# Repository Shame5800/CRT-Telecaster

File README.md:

Members

Shane Pomajambo, Electrical Engineering Student (2026)
Shanepomajambo16@vt.edu

Mentor

Arthur Ball

Current Status

IN PROGRESS

Project Overview

The purpose of this project is to create the CRT Telecaster guitars used by the Band ELECTRONICOS FANTASTICOS (https://www.youtube.com/@ELECTRONICOSFANTASTICOS_YT). The instrument sends 0V to 1V audio signals such as square, sine, and triangle waves to the video jack of a CRT television. This visualizes the waveform in the form of white and black bars, where white is high and black is low. Since CRT televisions are significant sources of electric fields, the audio signal fed into the video jack will become part of these fields, and the field’s rate of change will be the audio’s frequency with the CRT's internal frequencies. 

The note playing is caused by the concept of capacitive coupling. When the user touches the screen of the CRT, the screen and the user's hand form a parallel plate capacitor. On the board, there's an op-amp buffer that takes its input from a small trace and sends the output to an external speaker. When the instrument is in playing position, the trace is in proximity to the user's torso and is far away from any ground fills. This forms a series capacitor network formed by the hand-to-screen capacitance, the torso-to-trace capacitance, and the parasitic capacitance of the op-amp buffer trace. The changing E-field of the CRT creates displacement current on the network, which means the audio signal input to the CRT can be picked up by the capacitor network and sent to the speaker. Since the smallest capacitor in a series capacitor network sees the largest amount of voltage, the user can then change the volume of the note by bringing their hand closer or farther to the screen, which changes the capacitance ratios of the network that determine how much the op-amp buffer sees. 

The design of this instrument uses a driver PCB equipped with an ESP32 and a button array PCB meant to resemble a guitar fretboard. The board is equipped with 4 DAC channels and a non-inverting summing amplifier that leads to the CRT video input. In order to determine the fret being played, the fretboard PCB connects resistor dividers that are read by the ESP32’s ADCs. Each fret is designed to be 0.15V away from eachother, so that the ESP32’s 12-bit resolution sees it as being 200 counts away from eachother and has enough space to provide accurate readings. Once the user inputs a note on the fretboard, the ESP32 uses interrupt-style code to communicate to the DAC’s and have them output the musical frequencies. The driver board also comes equipped with a variety of switches and potentiometers to handle different musical effects and synth waveform structures. The user can alternate between 8 wave types, octaver, and warble effects, as well as bass, 5-string bass, and guitar options.

As of Summer 2026, the V2 of this project has finished development, and the V3 platform is currently in development. The next variation aims to improve mistakes from the previous iteration, including easier-to-access switches and a more ergonomic fretboard, and fixing SPI bus issues encountered in V2’s integration. It also aims to introduce new features, such as a touchscreen LCD allowing the user to draw the waveform that will be generated, more audio effects, and an internal programmable drum machine connected to the CRT’s speakers.

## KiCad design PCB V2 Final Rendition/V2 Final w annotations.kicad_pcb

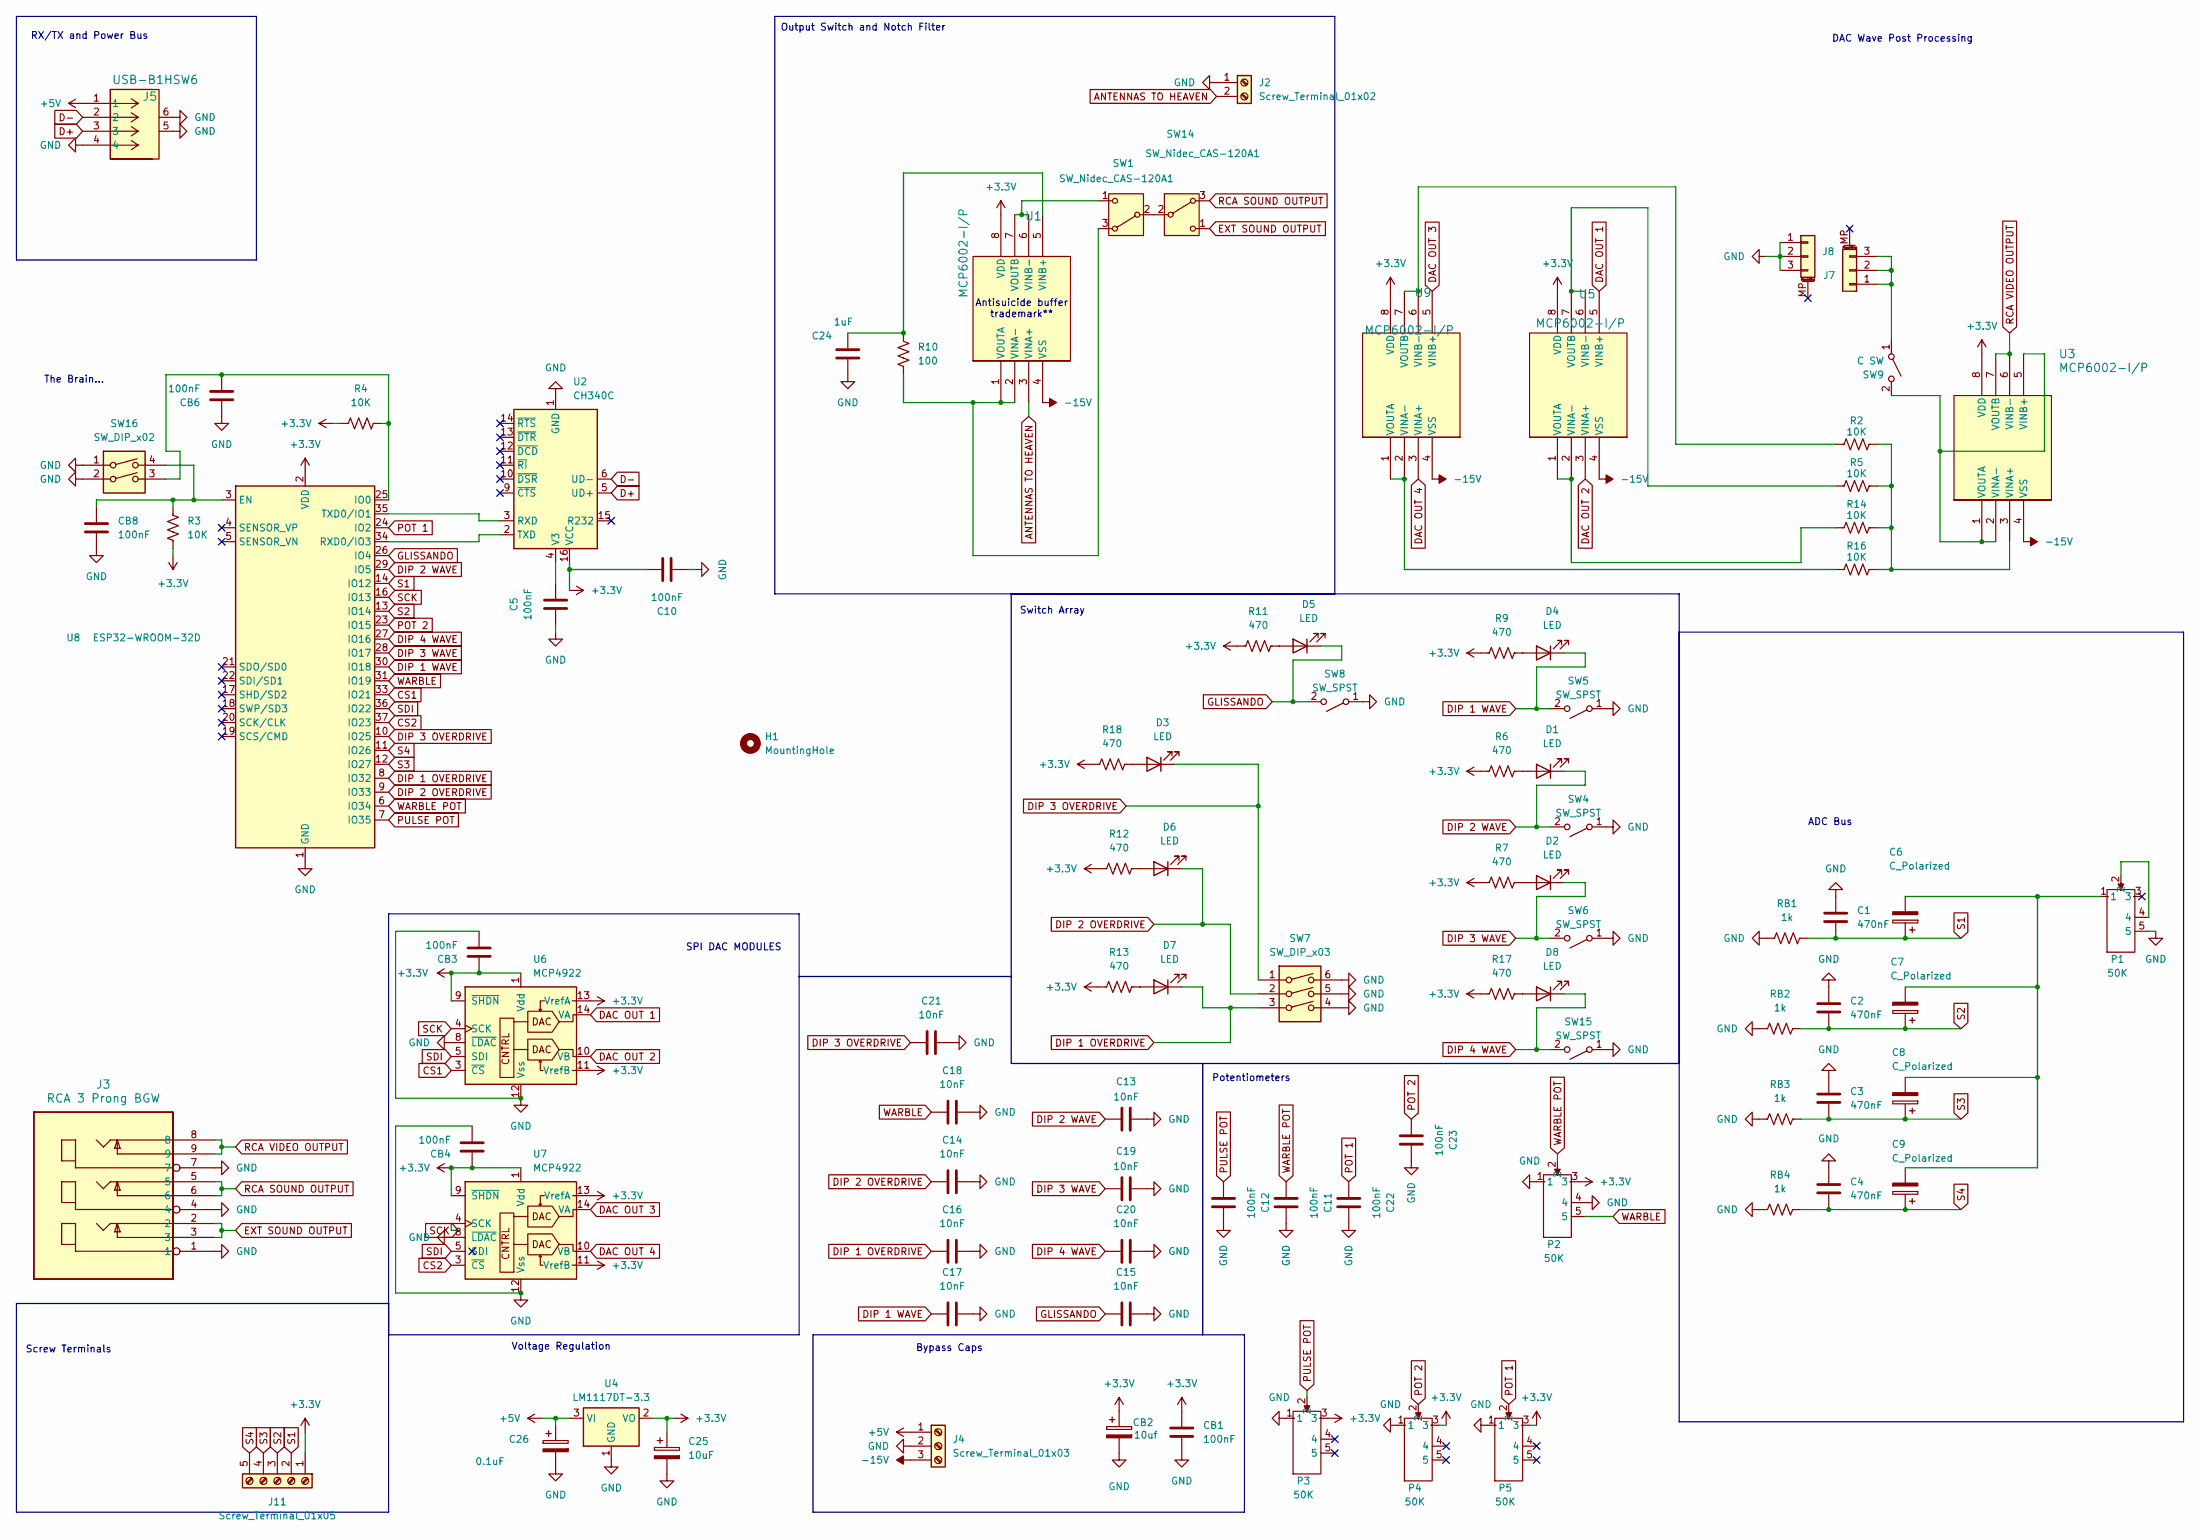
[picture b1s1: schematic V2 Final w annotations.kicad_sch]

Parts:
C1, C2, C3, C4: 470nF; C_Disc_D8.0mm_W2.5mm_P5.00mm
C5, C10, C11, C12, C22, C23: 100nF; C_0805_2012Metric_Pad1.18x1.45mm_HandSolder
C6, C7, C8, C9: C_Polarized; CP_Radial_D4.0mm_P2.00mm
C13, C14, C15, C16, C17, C18, C19, C20, C21: 10nF; C_0805_2012Metric_Pad1.18x1.45mm_HandSolder
C24: 1uF; C_Disc_D8.0mm_W2.5mm_P5.00mm
C25: 10uF; CP_Radial_D4.0mm_P2.00mm
C26: 0.1uF; CP_Radial_D4.0mm_P2.00mm
CB1, CB6: 100nF; C_0805_2012Metric_Pad1.18x1.45mm_HandSolder
CB2: 10uf; CP_Radial_D4.0mm_P2.00mm
CB3, CB4, CB8: 100nF; C_0805_2012Metric
D1, D2, D4, D5, D8: LED; LED_D3.0mm
D3, D6, D7: LED; LED_0805_2012Metric
H1: MountingHole; MountingHole_3.2mm_M3
J2: Screw_Terminal_01x02; TerminalBlock_MaiXu_MX126-5.0-02P_1x02_P5.00mm
J3: RCA 3 Prong BGW; RCA 3 Prong
J4: Screw_Terminal_01x03; TerminalBlock_MaiXu_MX126-5.0-03P_1x03_P5.00mm
J5: USB-B1HSW6; USB B Port
J7, J8: Conn_01x03_MountingPin; PinSocket_1x03_P2.54mm_Vertical
J11: Screw_Terminal_01x05; TerminalBlock_MaiXu_MX126-5.0-05P_1x05_P5.00mm
P1, P2, P3, P4, P5: 50K; ALPS POT SWITCH
R2, R5, R14, R16: 10K; R_Axial_DIN0207_L6.3mm_D2.5mm_P7.62mm_Horizontal
R3, R4: 10K; R_0805_2012Metric
R6, R7, R9, R11, R17: 470; R_Axial_DIN0207_L6.3mm_D2.5mm_P7.62mm_Horizontal
R10: 100; R_Axial_DIN0207_L6.3mm_D2.5mm_P7.62mm_Horizontal
R12, R13, R18: 470; R_0805_2012Metric
RB1, RB2, RB3, RB4: 1k; R_Axial_DIN0207_L6.3mm_D2.5mm_P7.62mm_Horizontal
SW1, SW14: SW_Nidec_CAS-120A1; SW_Slide_SPDT_Straight_CK_OS102011MS2Q
SW4, SW5, SW6, SW8, SW15: SW_SPST; SW_Slide_SPDT_Straight_CK_OS102011MS2Q
SW7: SW_DIP_x03; SW_DIP_SPSTx03_Slide_9.78x9.8mm_W7.62mm_P2.54mm
SW9: C SW; SW_Slide_SPDT_Straight_CK_OS102011MS2Q
SW16: SW_DIP_x02; SW_DIP_SPSTx02_Slide_9.78x7.26mm_W7.62mm_P2.54mm
U1, U3, U5, U9: MCP6002-I/P; MCP6002
U2: CH340C; SOIC-16_3.9x9.9mm_P1.27mm
U4: LM1117DT-3.3; SOT-223-3_TabPin2
U6, U7: MCP4922
U8: ESP32-WROOM-32D; esp32 WROOM without that FUCKASS attenna

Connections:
+3.3V: C10.1, C25.1, CB1.2, CB2.1, CB3.2, CB4.2, J11.1, P2.3, P3.3, P4.3, P5.3, R3.2, R4.1, R6.1, R7.1, R9.1, R11.1, R12.1, R13.1, R17.1, R18.1, U1.8 (VDD), U2.16 (VCC), U3.8 (VDD), U4.2 (VO), U5.8 (VDD), U6.1 (Vdd), U6.9 (~SHDN), U6.11 (VrefB), U6.13 (VrefA), U7.1 (Vdd), U7.9 (~SHDN), U7.11 (VrefB), U7.13 (VrefA), U8.2 (VDD), U9.8 (VDD)
+5V: C26.1, J4.1, J5.1, U4.3 (VI)
-15V: J4.3, U1.4 (VSS), U3.4 (VSS), U5.4 (VSS), U9.4 (VSS)
ANTENNAS TO HEAVEN: J2.2, U1.3 (VINA+)
CS1: U6.3 (~CS), U8.33 (IO21)
CS2: U7.3 (~CS), U8.37 (IO23)
D+: J5.3, U2.5 (UD+)
D-: J5.2, U2.6 (UD-)
DAC OUT 1: U5.5 (VINB+), U6.14 (VA)
DAC OUT 2: U5.3 (VINA+), U6.10 (VB)
DAC OUT 3: U7.14 (VA), U9.5 (VINB+)
DAC OUT 4: U7.10 (VB), U9.3 (VINA+)
DIP 1 OVERDRIVE: C16.2, D7.1 (K), SW7.3, U8.8 (IO32)
DIP 1 WAVE: C17.2, D4.1 (K), SW5.2 (B), U8.30 (IO18)
DIP 2 OVERDRIVE: C14.2, D6.1 (K), SW7.2, U8.9 (IO33)
DIP 2 WAVE: C13.2, D1.1 (K), SW4.2 (B), U8.29 (IO5)
DIP 3 OVERDRIVE: C21.2, D3.1 (K), SW7.1, U8.10 (IO25)
DIP 3 WAVE: C19.2, D2.1 (K), SW6.2 (B), U8.28 (IO17)
DIP 4 WAVE: C20.2, D8.1 (K), SW15.2 (B), U8.27 (IO16)
EXT SOUND OUTPUT: J3.2, J3.3, SW14.1 (C)
GLISSANDO: C15.2, D5.1 (K), SW8.2 (B), U8.26 (IO4)
GND: C1.1, C2.1, C3.1, C4.1, C5.2, C10.2, C11.1, C12.1, C13.1, C14.1, C15.1, C16.1, C17.1, C18.1, C19.1, C20.1, C21.1, C22.1, C23.1, C24.1, C25.2, C26.2, CB1.1, CB2.2, CB3.1, CB4.1, CB6.2, CB8.1, J2.1, J3.1, J3.4, J3.7, J4.2, J5.4, J5.5, J5.6, J8.1, J8.2, J8.3, P1.5, P2.1, P2.4, P3.1, P4.1, P5.1, RB1.1, RB2.1, RB3.1, RB4.1, SW4.1 (A), SW5.1 (A), SW6.1 (A), SW7.4, SW7.5, SW7.6, SW8.1 (A), SW15.1 (A), SW16.1, SW16.2, U2.1 (GND), U4.1 (GND), U6.8 (~LDAC), U6.12 (Vss), U7.8 (~LDAC), U7.12 (Vss), U8.1 (GND), U8.15 (GND), U8.38 (GND), U8.39 (GND)
unnamed: C6.2, C7.2, C8.2, C9.2, P1.1
unnamed: D1.2 (A), R6.2
unnamed: D2.2 (A), R7.2
unnamed: D3.2 (A), R18.2
unnamed: D4.2 (A), R9.2
unnamed: D5.2 (A), R11.2
unnamed: D6.2 (A), R12.2
unnamed: D7.2 (A), R13.2
unnamed: D8.2 (A), R17.2
unnamed: J7.1, J7.2, J7.3, SW9.1 (A)
unnamed: P1.2, P1.4
unnamed: R10.1, SW1.3 (A), U1.1 (VOUTA), U1.2 (VINA-)
unnamed: SW1.2 (B), SW14.2 (B)
unnamed: SW1.1 (C), U1.6 (VINB-), U1.7 (VOUTB)
unnamed: SW9.2 (B), U3.1 (VOUTA), U3.2 (VINA-), U3.5 (VINB+)
unnamed: C24.2, R10.2, U1.5 (VINB+)
unnamed: U2.3 (RXD), U8.35 (TXD0/IO1)
unnamed: U2.2 (TXD), U8.34 (RXD0/IO3)
unnamed: C5.1, U2.4 (V3)
unnamed: R2.2, R5.2, R14.2, R16.2, U3.3 (VINA+)
unnamed: R14.1, U5.1 (VOUTA), U5.2 (VINA-)
unnamed: R5.1, U5.6 (VINB-), U5.7 (VOUTB)
unnamed: CB8.2, R3.1, SW16.4, U8.3 (EN)
unnamed: CB6.1, R4.2, SW16.3, U8.25 (IO0)
unnamed: R16.1, U9.1 (VOUTA), U9.2 (VINA-)
unnamed: R2.1, U9.6 (VINB-), U9.7 (VOUTB)
POT 1: C22.2, P5.2, U8.24 (IO2)
POT 2: C23.2, P4.2, U8.23 (IO15)
PULSE POT: C12.2, P3.2, U8.7 (IO35)
RCA SOUND OUTPUT: J3.5, J3.6, SW14.3 (A)
RCA VIDEO OUTPUT: J3.8, J3.9, U3.6 (VINB-), U3.7 (VOUTB)
S1: C1.2, C6.1, J11.2, RB1.2, U8.14 (IO12)
S2: C2.2, C7.1, J11.3, RB2.2, U8.13 (IO14)
S3: C3.2, C8.1, J11.4, RB3.2, U8.12 (IO27)
S4: C4.2, C9.1, J11.5, RB4.2, U8.11 (IO26)
SCK: U6.4 (SCK), U7.4 (SCK), U8.16 (IO13)
SDI: U6.5 (SDI), U7.5 (SDI), U8.36 (IO22)
WARBLE: C18.2, P2.5, U8.31 (IO19)
WARBLE POT: C11.2, P2.2, U8.6 (IO34)

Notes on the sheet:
ADC Bus
Potentiometers
Output Switch and Notch Filter
Switch Array
Antisuicide buffer trademark**
SPI DAC MODULES
DAC Wave Post Processing
Screw Terminals
Voltage Regulation
Bypass Caps
The Brain...
RX/TX and Power Bus

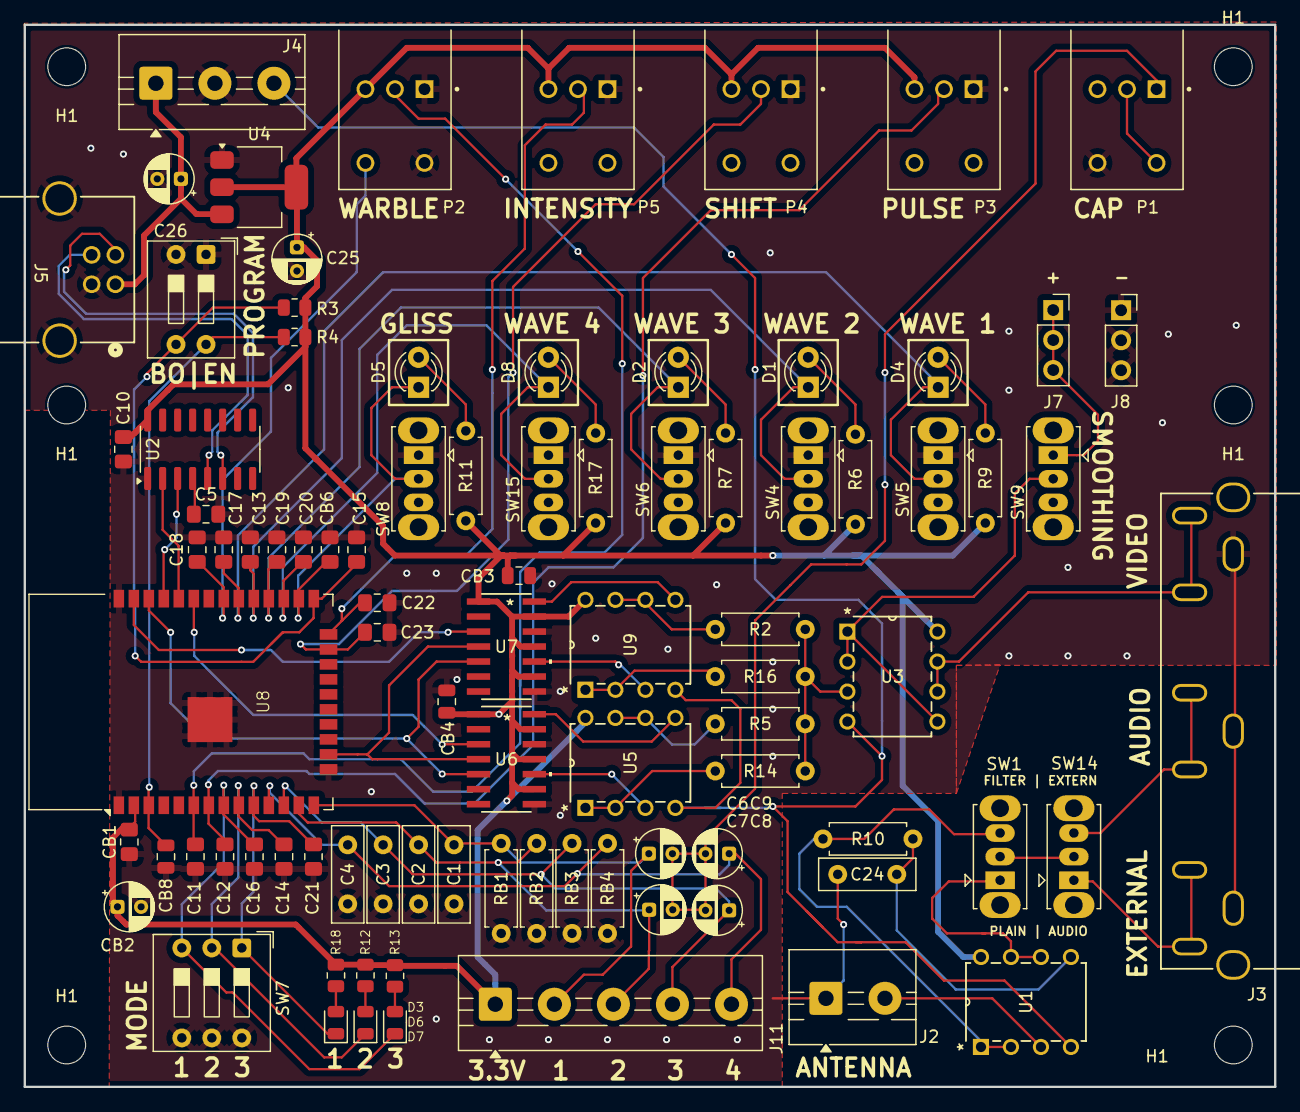
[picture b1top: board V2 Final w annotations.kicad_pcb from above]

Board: 2 copper layers, 105.9 x 89.9 mm, 96 parts (0 on the bottom side), 61 nets.

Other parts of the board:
H1#2, H1#3, H1#4, H1#5, H1#6: MountingHole; MountingHole_3.2mm_M3

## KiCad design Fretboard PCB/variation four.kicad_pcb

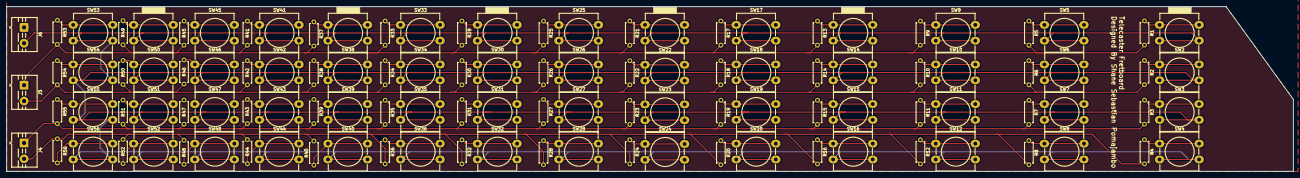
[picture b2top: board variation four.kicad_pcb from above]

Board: 2 copper layers, 406.2 x 52.0 mm, 115 parts (0 on the bottom side), 61 nets.

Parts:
J4, J5, J6: Screw_Terminal_01x02; TerminalBlock_MaiXu_MX126-5.0-02P_1x02_P5.00mm
R1, R2, R3, R4: 5K; R_Axial_DIN0207_L6.3mm_D2.5mm_P7.62mm_Horizontal
R5, R6, R7, R8: 3.6K; R_Axial_DIN0207_L6.3mm_D2.5mm_P7.62mm_Horizontal
R9, R10, R11, R12: 3K; R_Axial_DIN0207_L6.3mm_D2.5mm_P7.62mm_Horizontal
R13, R14, R15, R16: 2.2K; R_Axial_DIN0207_L6.3mm_D2.5mm_P7.62mm_Horizontal
R17, R18, R19, R20: 1.8K; R_Axial_DIN0207_L6.3mm_D2.5mm_P7.62mm_Horizontal
R21, R22, R23, R24: 1.5K; R_Axial_DIN0207_L6.3mm_D2.5mm_P7.62mm_Horizontal
R25, R26, R27, R28: 1.2K; R_Axial_DIN0207_L6.3mm_D2.5mm_P7.62mm_Horizontal
R29, R30, R31, R32: 1K; R_Axial_DIN0207_L6.3mm_D2.5mm_P7.62mm_Horizontal
R33, R34, R35, R36: 820; R_Axial_DIN0207_L6.3mm_D2.5mm_P7.62mm_Horizontal
R37, R38, R39, R40: 680; R_Axial_DIN0207_L6.3mm_D2.5mm_P7.62mm_Horizontal
R41, R42, R43, R44: 560; R_Axial_DIN0207_L6.3mm_D2.5mm_P7.62mm_Horizontal
R45, R46, R47, R48: 390; R_Axial_DIN0207_L6.3mm_D2.5mm_P7.62mm_Horizontal
R49, R50, R51, R52: 330; R_Axial_DIN0207_L6.3mm_D2.5mm_P7.62mm_Horizontal
R53, R54, R55, R56: 270; R_Axial_DIN0207_L6.3mm_D2.5mm_P7.62mm_Horizontal
SW1, SW2, SW3, SW4, SW5, SW6, SW7, SW8, SW9, SW10, SW11, SW12, SW13, SW14, SW15, SW16, SW17, SW18, SW19, SW20, SW21, SW22, SW23, SW24, SW25, SW26, SW27, SW28, SW29, SW30, SW31, SW32, SW33, SW34, SW35, SW36, SW37, SW38, SW39, SW40, SW41, SW42, SW43, SW44, SW45, SW46, SW47, SW48, SW49, SW50, SW51, SW52, SW53, SW54, SW55, SW56: SW_Push; SW_PUSH-12mm_Wuerth-430476085716

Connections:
+3.3V: J6.2, SW1.2, SW2.2, SW3.2, SW4.2, SW5.2, SW6.2, SW7.2, SW8.2, SW9.2, SW10.2, SW11.2, SW12.2, SW13.2, SW14.2, SW15.2, SW16.2, SW17.2, SW18.2, SW19.2, SW20.2, SW21.2, SW22.2, SW23.2, SW24.2, SW25.2, SW26.2, SW27.2, SW28.2, SW29.2, SW30.2, SW31.2, SW32.2, SW33.2, SW34.2, SW35.2, SW36.2, SW37.2, SW38.2, SW39.2, SW40.2, SW41.2, SW42.2, SW43.2, SW44.2, SW45.2, SW46.2, SW47.2, SW48.2, SW49.2, SW50.2, SW51.2, SW52.2, SW53.2, SW54.2, SW55.2, SW56.2
unnamed: R1.1, SW1.1
unnamed: R2.1, SW2.1
unnamed: R3.1, SW3.1
unnamed: R4.1, SW4.1
unnamed: R5.1, SW5.1
unnamed: R6.1, SW6.1
unnamed: R7.1, SW7.1
unnamed: R8.1, SW8.1
unnamed: R9.1, SW9.1
unnamed: R10.1, SW10.1
unnamed: R11.1, SW11.1
unnamed: R12.1, SW12.1
unnamed: R13.1, SW13.1
unnamed: R14.1, SW14.1
unnamed: R15.1, SW15.1
unnamed: R16.1, SW16.1
unnamed: R17.1, SW17.1
unnamed: R18.1, SW18.1
unnamed: R19.1, SW19.1
unnamed: R20.1, SW20.1
unnamed: R21.1, SW21.1
unnamed: R22.1, SW22.1
unnamed: R23.1, SW23.1
unnamed: R24.1, SW24.1
unnamed: R25.1, SW25.1
unnamed: R26.1, SW26.1
unnamed: R27.1, SW27.1
unnamed: R28.1, SW28.1
unnamed: R29.1, SW29.1
unnamed: R30.1, SW30.1
unnamed: R31.1, SW31.1
unnamed: R32.1, SW32.1
unnamed: R33.1, SW33.1
unnamed: R34.1, SW34.1
unnamed: R35.1, SW35.1
unnamed: R36.1, SW36.1
unnamed: R37.1, SW37.1
unnamed: R38.1, SW38.1
unnamed: R39.1, SW39.1
unnamed: R40.1, SW40.1
unnamed: R41.1, SW41.1
unnamed: R42.1, SW42.1
unnamed: R43.1, SW43.1
unnamed: R44.1, SW44.1
unnamed: R45.1, SW45.1
unnamed: R46.1, SW46.1
unnamed: R47.1, SW47.1
unnamed: R48.1, SW48.1
unnamed: R49.1, SW49.1
unnamed: R50.1, SW50.1
unnamed: R51.1, SW51.1
unnamed: R52.1, SW52.1
unnamed: R53.1, SW53.1
unnamed: R54.1, SW54.1
unnamed: R55.1, SW55.1
unnamed: R56.1, SW56.1
S1: J4.2, R4.2, R8.2, R12.2, R16.2, R20.2, R24.2, R28.2, R32.2, R36.2, R40.2, R44.2, R48.2, R52.2, R56.2
S2: J4.1, R3.2, R7.2, R11.2, R15.2, R19.2, R23.2, R27.2, R31.2, R35.2, R39.2, R43.2, R47.2, R51.2, R55.2
S3: J5.2, R2.2, R6.2, R10.2, R14.2, R18.2, R22.2, R26.2, R30.2, R34.2, R38.2, R42.2, R46.2, R50.2, R54.2
S4: J5.1, R1.2, R5.2, R9.2, R13.2, R17.2, R21.2, R25.2, R29.2, R33.2, R37.2, R41.2, R45.2, R49.2, R53.2

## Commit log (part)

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2026-03-31 Create test
2026-04-09 Create Changelog
2026-04-09 Update Changelog
2026-05-15 IT PLAYED MY HIGHSCHOOL BAND'S TUNING CHORALE! IM SO PROUD! (first wave producing source code [5/14/2026])
2026-05-20 In Memory Of Mr Martin. I hope you enjoy infinite aeropress coffee in heaven
2026-05-26 Working Prototype 1.1
2026-05-26 Added pitch shifter, made things more organized, added Yoshi's Island Tuning
2026-06-03 Adding new hero.png for amp lab thumbnail
2026-06-03 adding thumbnail
2026-06-03 test
2026-06-04 Create How to Access Codebase
2026-06-04 Cleaned up comments
